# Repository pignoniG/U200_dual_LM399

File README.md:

# U200_dual_LM399
Yet another LM399 reference

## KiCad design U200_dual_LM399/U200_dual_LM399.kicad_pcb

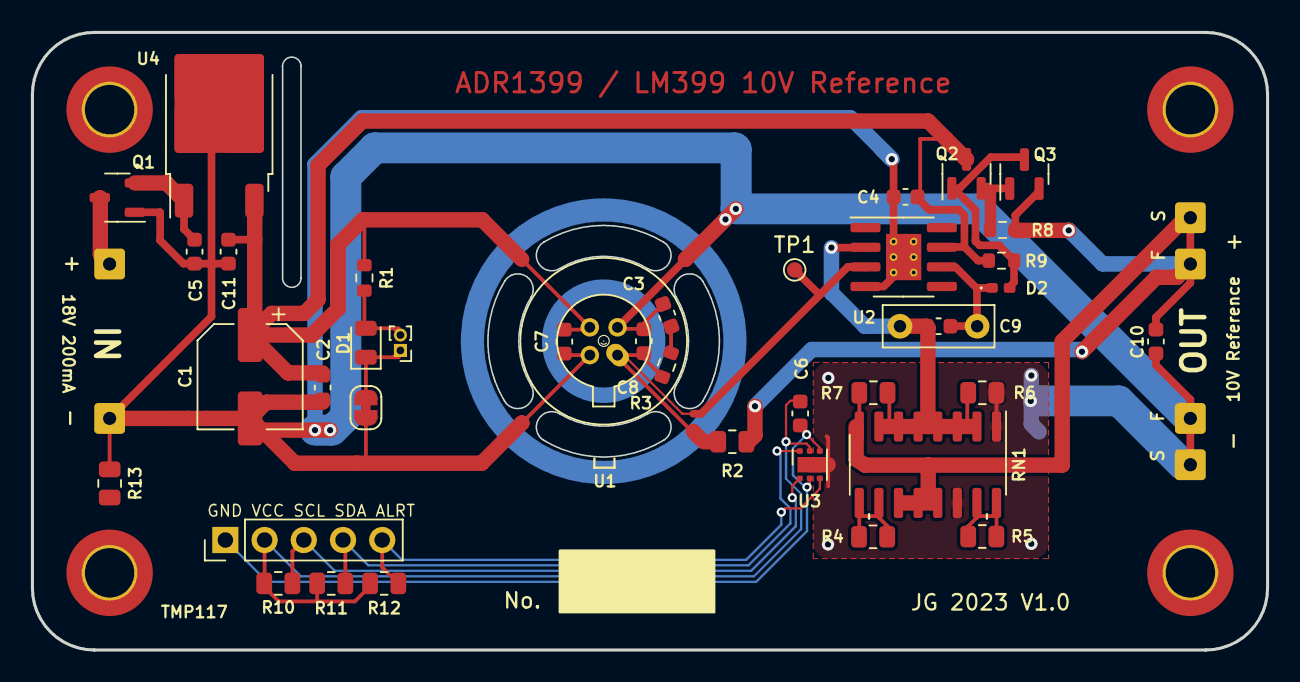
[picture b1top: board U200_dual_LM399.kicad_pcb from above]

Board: 2 copper layers, 80.0 x 40.0 mm, 45 parts (0 on the bottom side), 20 nets.

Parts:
C1: 20uF; CP_Elec_6.3x5.7
C2, C3, C4, C5: 1uF; C_0603_1608Metric
C6: 1u; C_0603_1608Metric
C7, C9, C10: 100n; C_0603_1608Metric
C8: opt; C_0603_1608Metric
C11: 100nF; C_0603_1608Metric
C12: opt footprint; C_Rect_L7.0mm_W2.5mm_P5.00mm
D1: LED; LED_0805_2012Metric
D2: BAS16L_G3-08; D_0402_1005Metric_Pad0.77x0.64mm_HandSolder
J1, J3, J7, J8: -; SolderWire-0.25sqmm_1x01_D0.65mm_OD2mm
J2, J4: +; SolderWire-0.25sqmm_1x01_D0.65mm_OD2mm
J5: Conn_01x02_Pin; PinHeader_1x02_P1.00mm_Vertical
J6: Conn_01x05; PinHeader_1x05_P2.54mm_Vertical
JP1: SolderJumper_2_Bridged; SolderJumper-2_P1.3mm_Bridged_RoundedPad1.0x1.5mm
Q1: DMP3099L-7; SOT-23-3
Q2, Q3: BC817; SOT-23
R1: 5k6; R_0603_1608Metric
R2: 1k; R_0805_2012Metric
R3: 5R1; R_0603_1608Metric
R4, R5, R6: opt; R_0805_2012Metric
R7: 118k; R_0805_2012Metric
R8: 20; R_0603_1608Metric
R9: 10k; R_0603_1608Metric
R10, R11, R12: 4k7; R_0805_2012Metric
R13: R; R_0805_2012Metric
RN1: NOMCT16031002AT1; SOIC-16_3.9x9.9mm_P1.27mm
TP1: TestPoint; TestPoint_Pad_D1.0mm
U1: LM399; Analog_TO-46-4_ThermalShield
U2: OPA202; SOIC-8-1EP_3.9x4.9mm_P1.27mm_EP2.29x3mm_ThermalVias
U3: TMP117; WSON-6-1EP_2x2mm_P0.65mm_EP1x1.6mm
U4: L7815; TO-252-2

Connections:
unnamed: C3.1, R3.2
unnamed: D1.2 (A), J5.2, R1.2
unnamed: D1.1 (K), J5.1, JP1.2 (B)
unnamed: D2.2 (A), Q2.1 (B), Q3.3 (C), R9.2
unnamed: C9.2, C12.2, D2.1 (K), U2.6
unnamed: C1.2, C2.2, C3.2, C4.2, C5.2, C7.2, C8.2, C10.2, C11.2, J1.1, J3.1, J7.1, JP1.1 (A), Q1.2 (G), R6.1, R13.1, RN1.1 (R1.1), RN1.14 (R3.2), U1.2, U1.4, U2.4 (V-), U4.2 (GND)
unnamed: J2.1, Q1.1 (D)
unnamed: C10.1, J4.1, J8.1, Q3.2 (E), R2.1, R7.2, R8.2, RN1.8 (R8.1), RN1.11 (R6.2), RN1.12 (R5.2), RN1.13 (R4.2)
unnamed: C6.2, J6.1, U3.2 (GND), U3.4 (ADD0)
unnamed: C6.1, J6.2, R10.1, R11.1, R12.1, U3.5 (V+)
unnamed: J6.3, R10.2, U3.1 (SCL)
unnamed: J6.4, R11.2, U3.6 (SDA)
unnamed: J6.5, R12.2, U3.3 (ALERT)
unnamed: C5.1, Q1.3 (S), U4.1 (IN)
unnamed: C1.1, C2.1, C4.1, C7.1, C11.1, Q2.3 (C), R1.1, R9.1, U1.3, U2.7 (V+), U4.3 (OUT)
unnamed: Q2.2 (E), Q3.1 (B), R8.1
unnamed: R5.1, R5.2, RN1.15 (R2.2), RN1.16 (R1.2)
unnamed: C9.1, C12.1, R6.2, R7.1, RN1.2 (R2.1), RN1.3 (R3.1), RN1.4 (R4.1), RN1.5 (R5.1), RN1.6 (R6.1), RN1.7 (R7.1), U2.2 (-)
unnamed: R4.1, R4.2, RN1.9 (R8.2), RN1.10 (R7.2)
unnamed: C8.1, R2.2, R3.1, TP1.1, U1.1, U2.3 (+)
